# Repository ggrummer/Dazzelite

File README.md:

# Dazzelite
Dazzelite is an easy to build project that uses a ring of tri-color LED lights, controlled by an FPGA, using a few simple instructions, to create different patterns of light. It can be built on a breadboard or in a beautiful case.

A video introduction can be seen at the following link:
https://vimeo.com/516437596

The "Documents" directory contains all the guides for building and using Dazzelite.

The "Dazz12" directory contains all the FPGA code.

The "EAGLE" directory contains the schematic, parts list and board design.

The "BreadBoardSchematic" contains the schematic for a simple breadboard version.

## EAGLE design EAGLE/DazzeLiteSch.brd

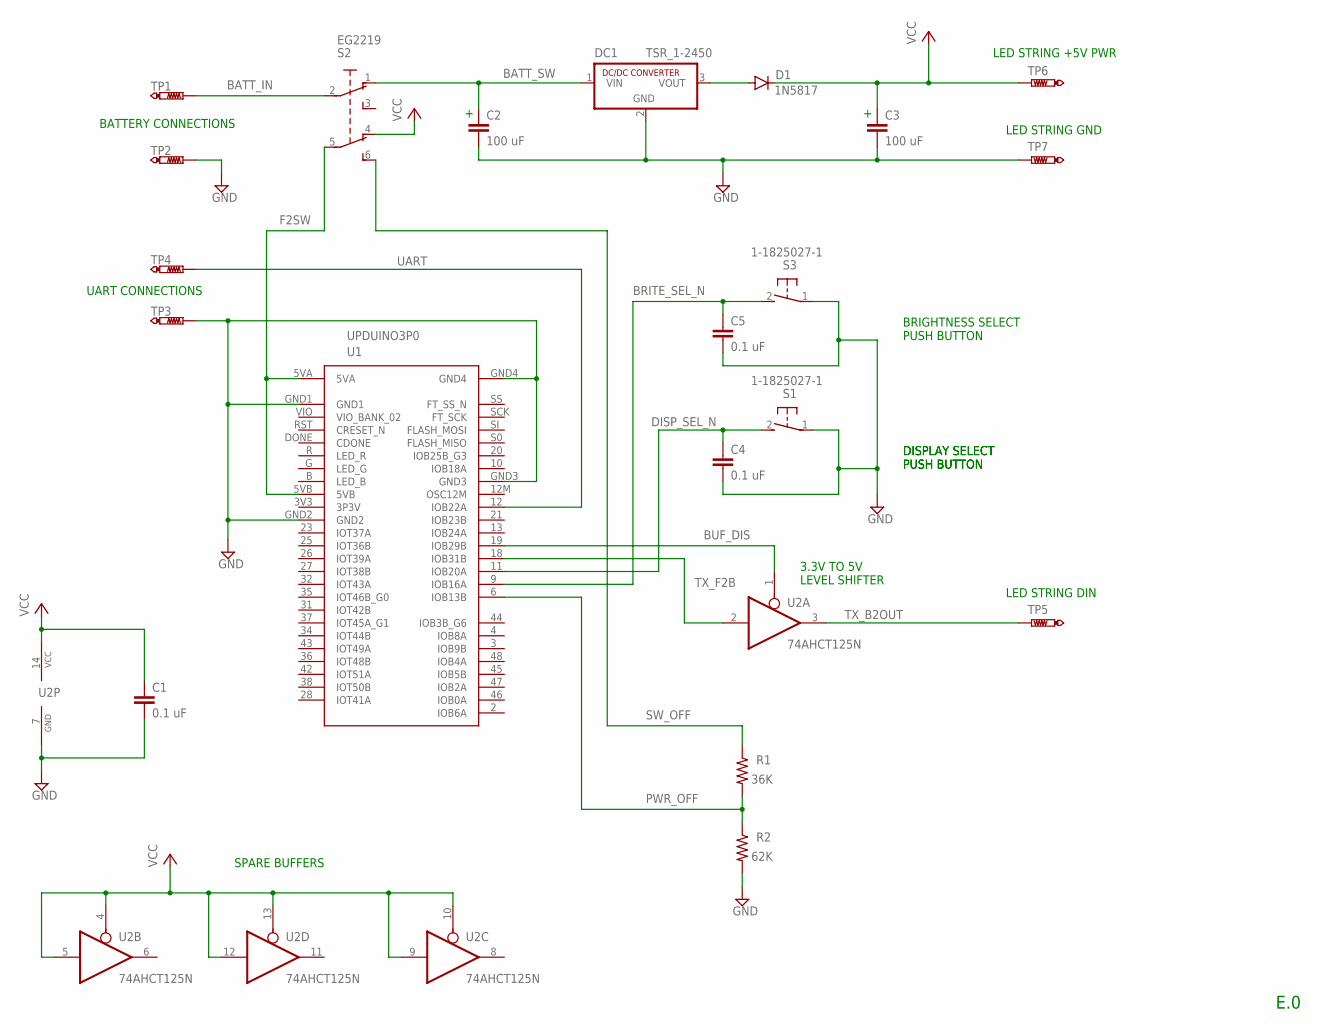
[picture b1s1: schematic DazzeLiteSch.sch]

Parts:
C1, C4, C5: 0.1 uF; C2.5-3
C2, C3: 100 uF; C2.5-6
D1: 1N5817; DO41-10
DC1: TSR_1-2450; SIP3
R1: 36K; 0204/7
R2: 62K; 0204/7
S1, S3: 1-1825027-1; B3F-31XX
S2: EG2219; DPDT157
TP1, TP2, TP3, TP4, TP5, TP6, TP7: PTR1PAD1-13; P1-13
U1: UPDUINO3P0
U2: 74AHCT125N; DIL14

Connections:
BATT_IN: S2.2, TP1.TP
BATT_SW: C2.1, DC1.1 (VIN), S2.1 (O)
BRITE_SEL_N: C5.1, S3.2 (S), U1.9 (IOB16A)
BUF_DIS: U1.19 (IOB29B), U2.1 (OE)
DISP_SEL_N: C4.1, S1.2 (S), U1.11 (IOB20A)
F2SW: S2.5 (P1), U1.5VA, U1.5VB
GND: C1.2, C2.2, C3.2, C4.2, C5.2, DC1.2 (GND), R2.2, S1.1, S3.1, TP2.TP, TP3.TP, TP7.TP, U1.GND1, U1.GND2, U1.GND3, U1.GND4, U2.7 (GND)
unnamed: D1.A, DC1.3 (VOUT)
PWR_OFF: R1.2, R2.1, U1.6 (IOB13B)
SW_OFF: R1.1, S2.6 (S1)
TX_B2OUT: TP5.TP, U2.3 (O)
TX_F2B: U1.18 (IOB31B), U2.2 (I)
UART: TP4.TP, U1.12 (IOB22A)
VCC: C1.1, C3.1, D1.C, S2.4 (O1), TP6.TP, U2.4 (OE), U2.5 (I), U2.9 (I), U2.10 (OE), U2.12 (I), U2.13 (OE), U2.14 (VCC)

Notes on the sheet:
LED STRING DIN
UART CONNECTIONS
BATTERY CONNECTIONS
LED STRING +5V PWR
LED STRING GND
E.0
DISPLAY SELECT PUSH BUTTON
3.3V TO 5V LEVEL SHIFTER
SPARE BUFFERS
BRIGHTNESS SELECT PUSH BUTTON

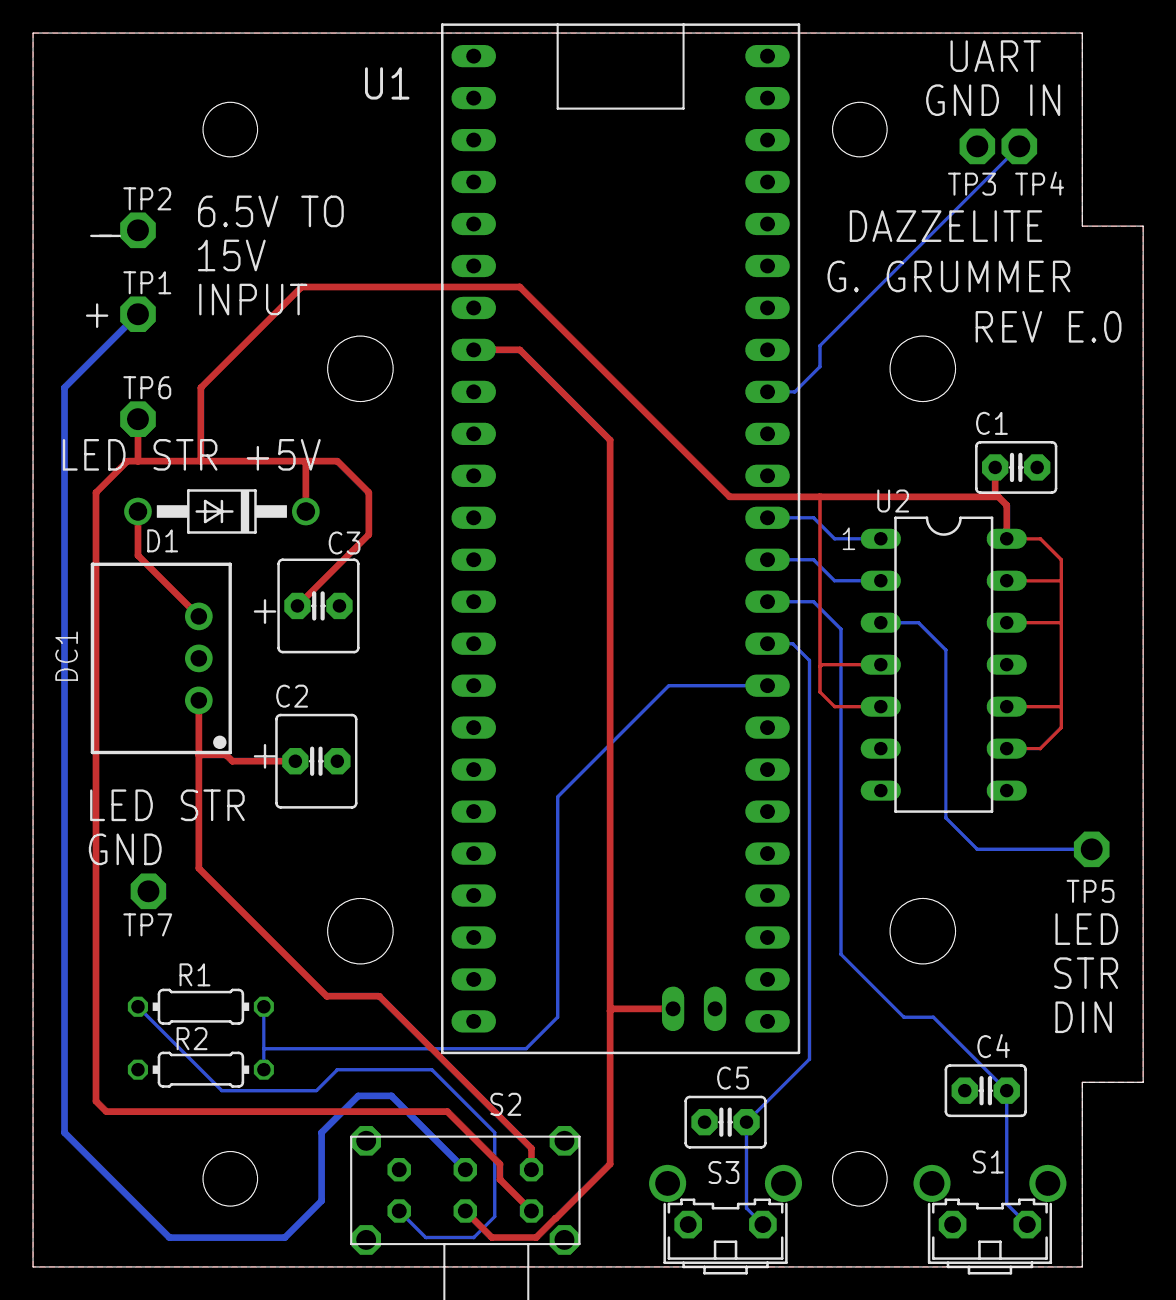
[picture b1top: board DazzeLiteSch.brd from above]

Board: 2 copper layers, 67.2 x 74.7 mm, 21 parts (0 on the bottom side), 14 nets.

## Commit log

2021-02-08 Rev E Changes
    New board rev includes new FPGA pinout and fix to power up detection circuit.
    Added functionality to chase module. One can now select step size.
2021-02-15 Update DazzelitePL.xlsx
    Reduced PCB cost.
2021-02-15 Deleted part list info. Refer to part list in Parts directory.
    Refer to part list in Parts directory.
2021-02-15 Corrected a few part numbers
2021-02-15 Update StarLiteLib.lbr
    Corrected a few part numbers
2021-02-18 Many changes
    Added schematic for a scaled down breadboard design.
    Updated instruction memories to block diagram.
    Moved parts list to EAGLE directory.
    Removed case cutout spreadsheet, will be replaced by assembly document.
2021-02-20 Added documentation.
    The "Assembly Instructions" and "Installation and Setup" manuals are in good shape. The "User's Manual" need a new link to the yet to be produced video.
2021-02-25 Initial release
2021-02-25 Update README.md
    Fixed typo
2021-02-26 Update Dazzelite User's Manual.pdf
    Fixed typo
2021-02-27 Update Dazzelite Assembly Instructions.pdf
    Added/updated some pictures.
2021-03-04 Update shootenballs.mem
    Increased the blue brightness.
2021-03-10 Update DazzelitePL.xlsx
    Changed 9V battery connector to one where the wires come out the side. This makes it easier to get the battery in & out.
